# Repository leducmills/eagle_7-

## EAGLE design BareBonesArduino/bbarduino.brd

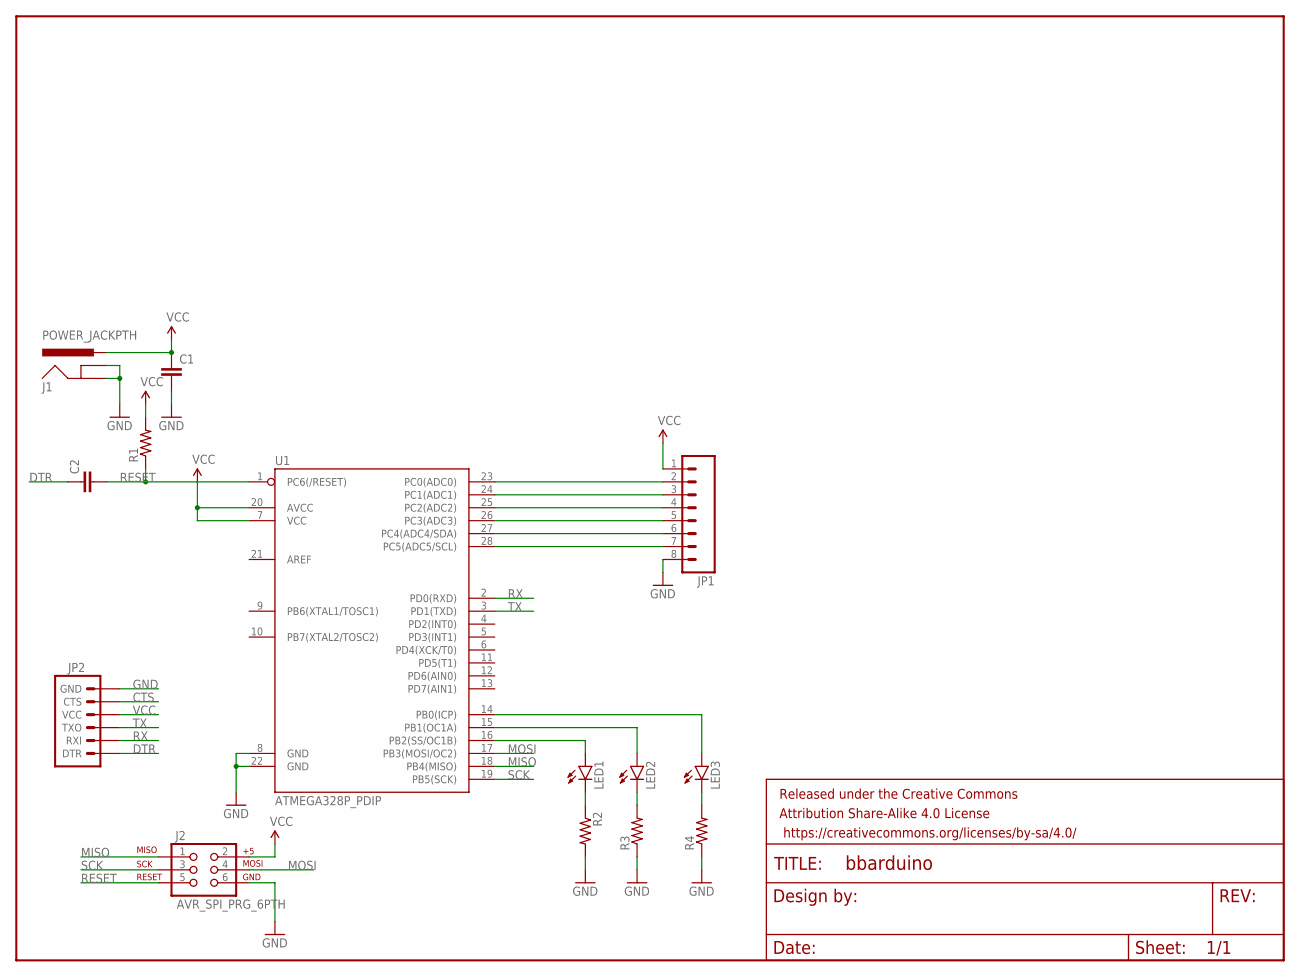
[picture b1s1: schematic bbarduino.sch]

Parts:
C1, C2: CAPPTH; CAP-PTH-SMALL
FRAME1: FRAME-LETTER; CREATIVE_COMMONS
J1: POWER_JACKPTH; POWER_JACK_PTH
J2: AVR_SPI_PRG_6PTH; 2X3
JP1: M081X08; 1X08
JP2: ARDUINO_SERIAL_PROGRAMPTH; 1X06
LED1, LED2, LED3: LED5MM
R1, R2, R3, R4: RESISTORPTH-1/4W; AXIAL-0.4
U1: ATMEGA328P_PDIP; DIL28-3

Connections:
CTS: JP2.CTS
DTR: C2.1, JP2.DTR
GND: C1.2, J1.GND, J1.GNDBREAK, J2.6, JP1.8, JP2.GND, R2.P$2 (2), R3.P$1 (1), R4.P$1 (1), U1.8 (GND), U1.22 (GND)
MISO: J2.1, U1.18 (PB4(MISO))
MOSI: J2.4, U1.17 (PB3(MOSI/OC2))
unnamed: LED1.K (C), R2.P$1 (1)
unnamed: JP1.2, U1.23 (PC0(ADC0))
unnamed: JP1.3, U1.24 (PC1(ADC1))
unnamed: JP1.4, U1.25 (PC2(ADC2))
unnamed: JP1.5, U1.26 (PC3(ADC3))
unnamed: JP1.6, U1.27 (PC4(ADC4/SDA))
unnamed: JP1.7, U1.28 (PC5(ADC5/SCL))
unnamed: LED1.A, U1.16 (PB2(SS/OC1B))
unnamed: LED2.A, U1.15 (PB1(OC1A))
unnamed: LED3.A, U1.14 (PB0(ICP))
unnamed: LED2.K (C), R3.P$2 (2)
unnamed: LED3.K (C), R4.P$2 (2)
RESET: C2.2, J2.5, R1.P$1 (1), U1.1 (PC6(/RESET))
RX: JP2.RXI, U1.2 (PD0(RXD))
SCK: J2.3, U1.19 (PB5(SCK))
TX: JP2.TXO, U1.3 (PD1(TXD))
VCC: C1.1, J1.PWR, J2.2, JP1.1, JP2.VCC, R1.P$2 (2), U1.7 (VCC), U1.20 (AVCC)

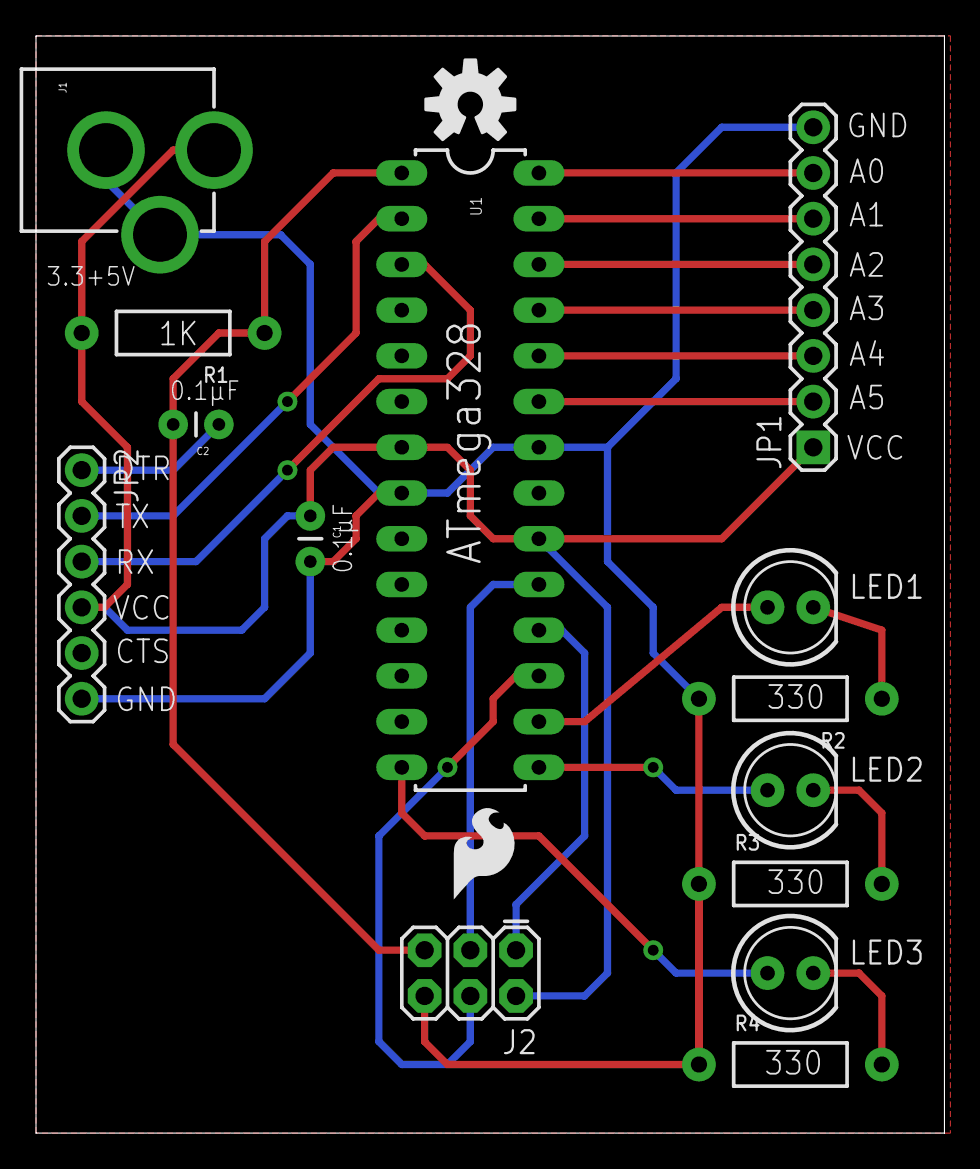
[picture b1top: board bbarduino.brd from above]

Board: 2 copper layers, 50.5 x 61.0 mm, 17 parts (0 on the bottom side), 21 nets.

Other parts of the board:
U$1: SFE_LOGO_FLAME_.2
U$2: OSHW-LOGO-M

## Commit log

2014-10-06 EagleProjects

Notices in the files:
parts and their libraries:
SparkFun-Capacitors: Licensing: Creative Commons ShareAlike 4.0 International - https://creativecommons.org/licenses/by-sa/4.0
SparkFun-Aesthetics: Released under the Creative Commons Attribution Share-Alike 4.0 License
SparkFun-Aesthetics: https://creativecommons.org/licenses/by-sa/4.0
